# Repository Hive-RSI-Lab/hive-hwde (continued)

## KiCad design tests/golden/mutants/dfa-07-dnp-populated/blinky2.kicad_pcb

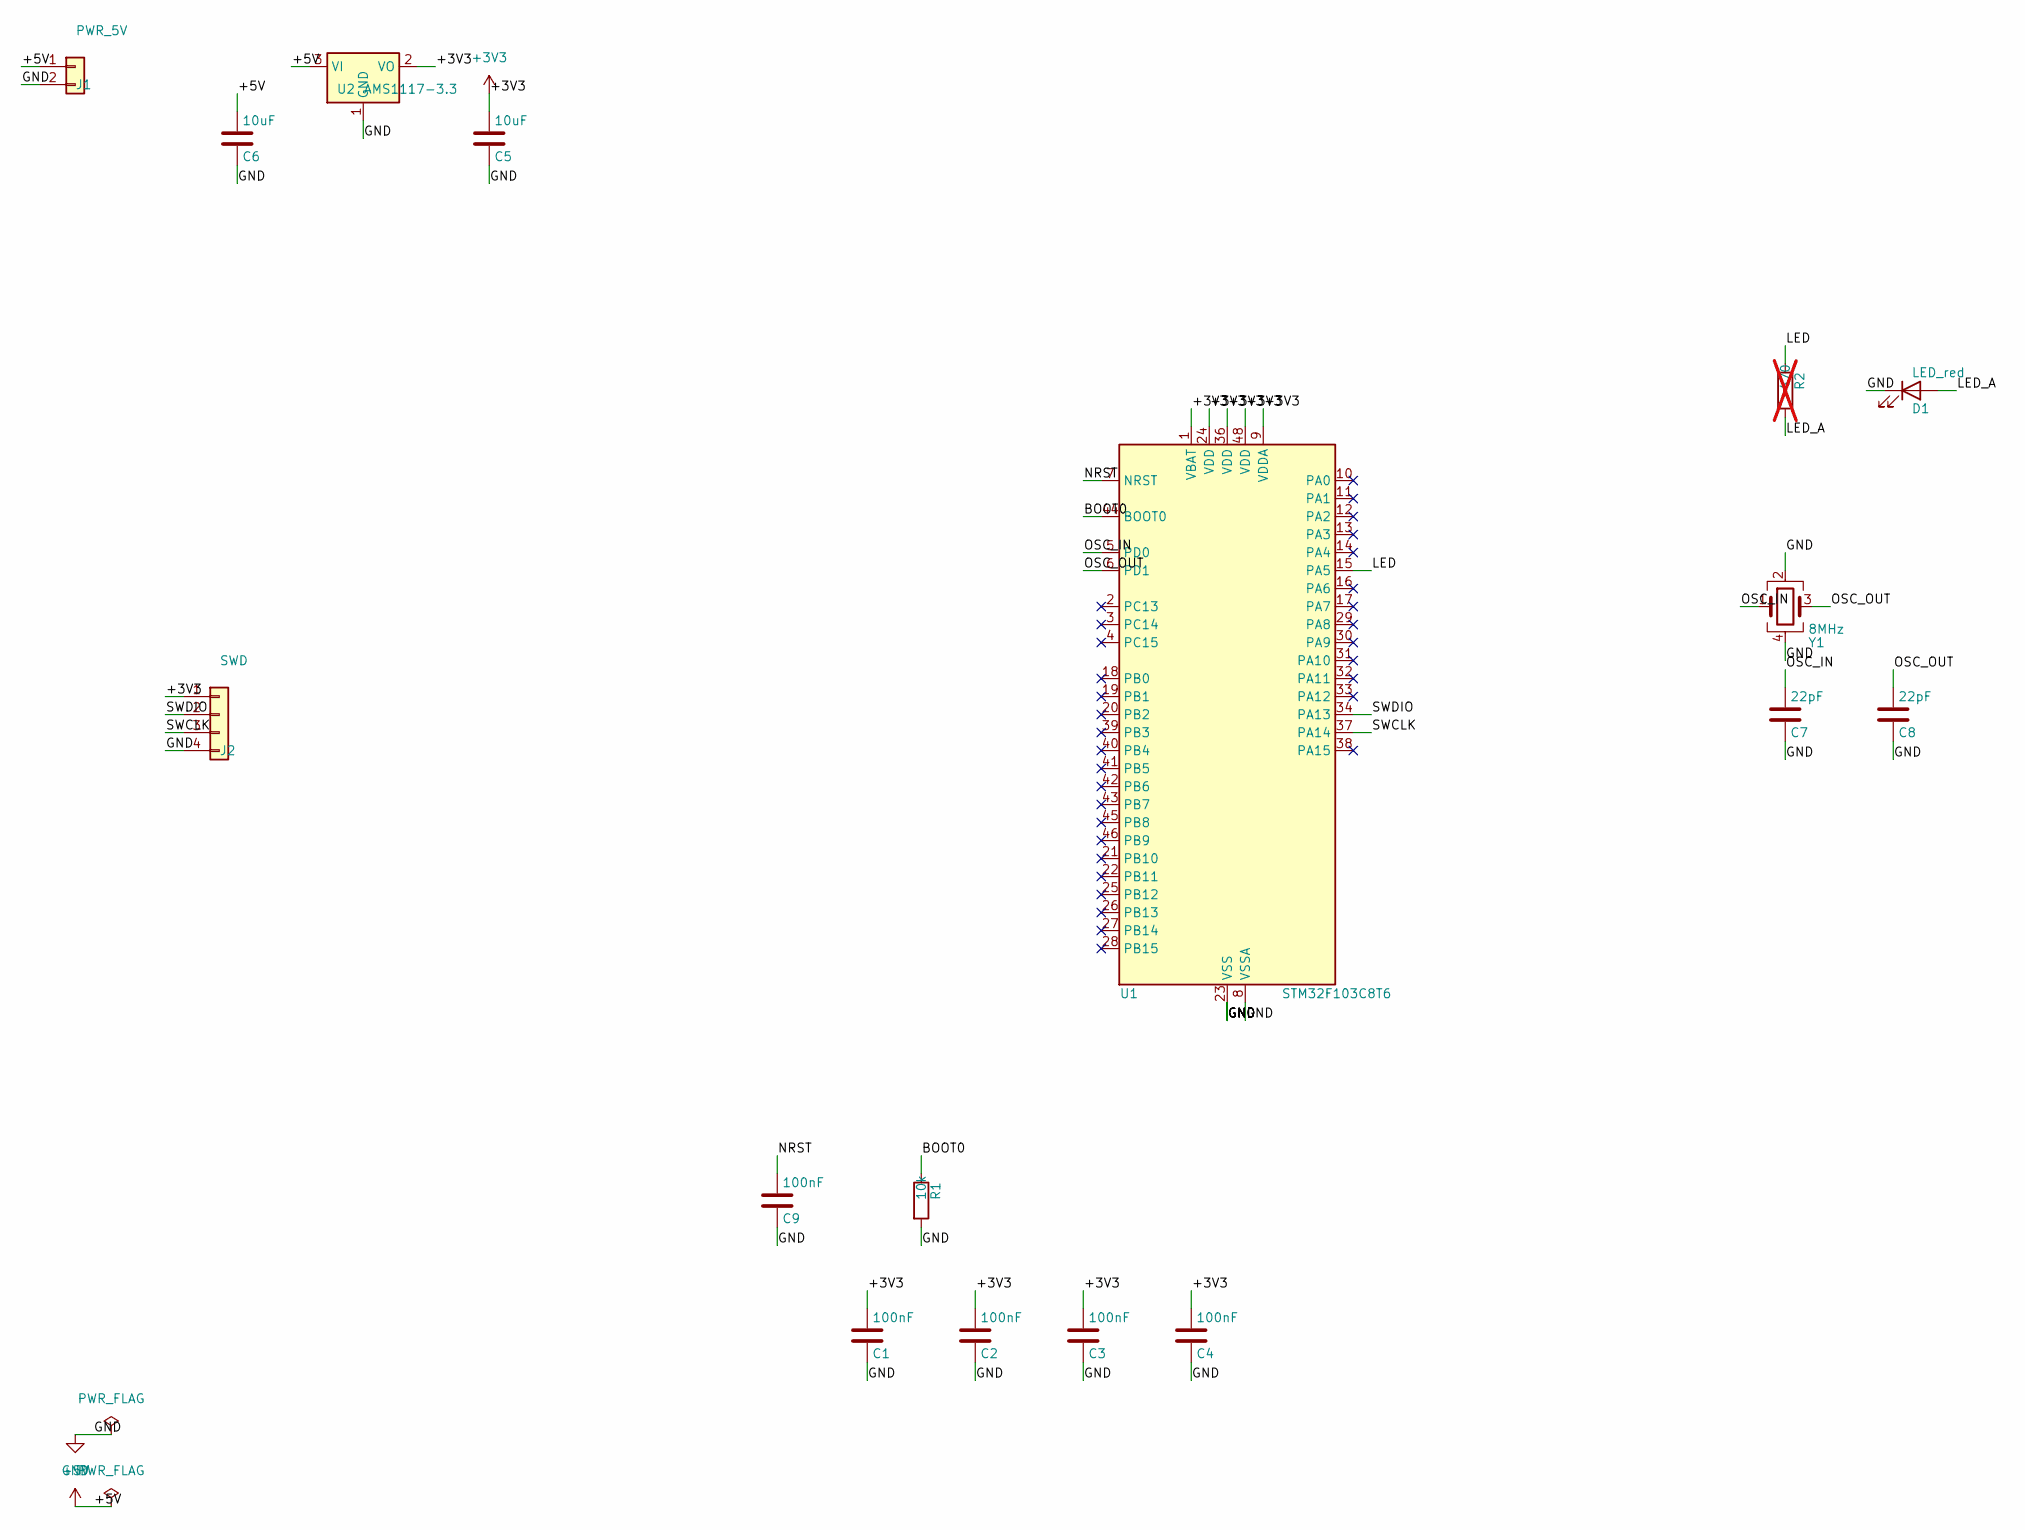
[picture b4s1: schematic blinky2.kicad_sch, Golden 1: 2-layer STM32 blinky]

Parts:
C1, C2, C3, C4, C9: 100nF; C_0603_1608Metric
C5, C6: 10uF; C_0805_2012Metric
C7, C8: 22pF; C_0603_1608Metric
D1: LED_red; LED_0805_2012Metric
J1: PWR_5V; PinHeader_1x02_P2.54mm_Vertical
J2: SWD; PinHeader_1x04_P2.54mm_Vertical
R1: 10k; R_0603_1608Metric
R2: 470; R_0603_1608Metric; not fitted
U1: STM32F103C8T6; LQFP-48_7x7mm_P0.5mm
U2: AMS1117-3.3; SOT-223-3_TabPin2
Y1: 8MHz; Crystal_SMD_3225-4Pin_3.2x2.5mm

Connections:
+3V3: C1.1, C2.1, C3.1, C4.1, C5.1, J2.1, U1.1 (VBAT), U1.9 (VDDA), U1.24 (VDD), U1.36 (VDD), U1.48 (VDD), U2.2 (VO)
+5V: C6.1, J1.1, U2.3 (VI)
/BOOT0: R1.1, U1.44 (BOOT0)
/LED: R2.1, U1.15 (PA5)
/LED_A: D1.2 (A), R2.2
/NRST: C9.1, U1.7 (NRST)
/OSC_IN: C7.1, U1.5 (PD0), Y1.1
/OSC_OUT: C8.1, U1.6 (PD1), Y1.3
/SWCLK: J2.3, U1.37 (PA14)
/SWDIO: J2.2, U1.34 (PA13)
GND: C1.2, C2.2, C3.2, C4.2, C5.2, C6.2, C7.2, C8.2, C9.2, D1.1 (K), J1.2, J2.4, R1.2, U1.8 (VSSA), U1.23 (VSS), U1.35 (VSS), U1.47 (VSS), U2.1 (GND), Y1.2, Y1.4

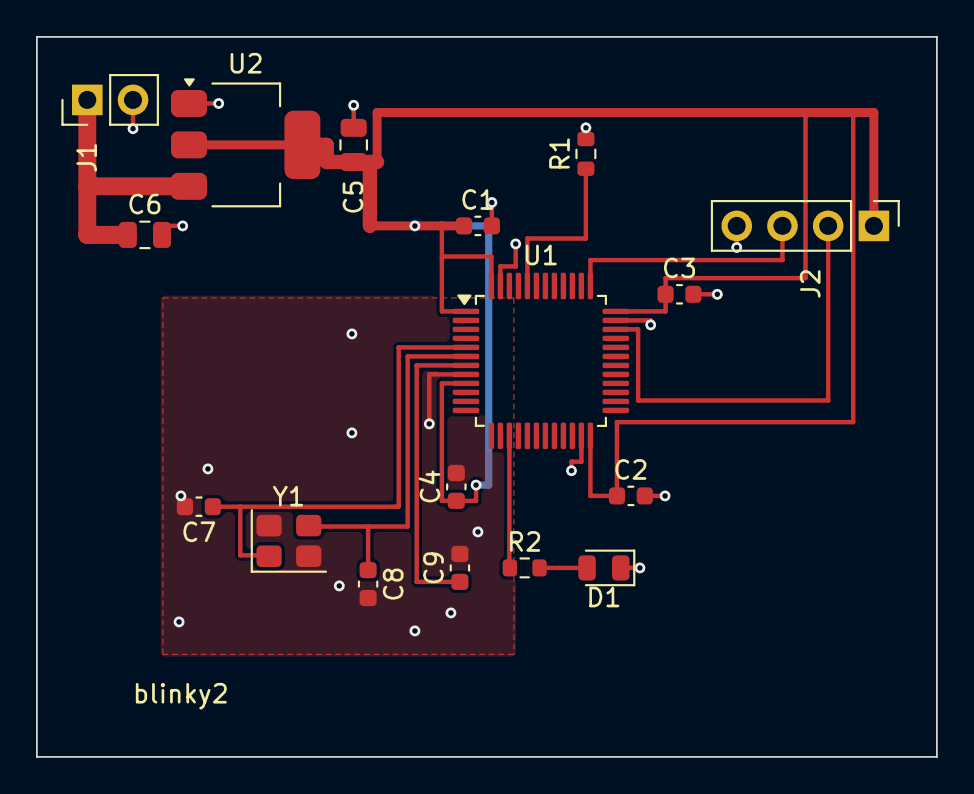
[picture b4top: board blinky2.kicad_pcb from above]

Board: 2 copper layers, 50.0 x 40.0 mm, 17 parts (0 on the bottom side), 11 nets.

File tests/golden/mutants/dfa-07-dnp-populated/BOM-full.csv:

Comment,Designator,Qty Per Board,Footprint,MPN,LCSC,Assembly Class,Instructions
PWR_5V,J1,1,PinHeader_1x02_P2.54mm_Vertical,,,smt_placed,
SWD,J2,1,PinHeader_1x04_P2.54mm_Vertical,,,smt_placed,
22pF,"C8,C7",2,C_0603_1608Metric,,,smt_placed,
10uF,"C5,C6",2,C_0805_2012Metric,,,smt_placed,
8MHz,Y1,1,Crystal_SMD_3225-4Pin_3.2x2.5mm,,,smt_placed,
100nF,"C9,C1,C2,C3,C4",5,C_0603_1608Metric,,,smt_placed,
10k,R1,1,R_0603_1608Metric,,,smt_placed,
STM32F103C8T6,U1,1,LQFP-48_7x7mm_P0.5mm,,,smt_placed,
AMS1117-3.3,U2,1,SOT-223-3_TabPin2,,,smt_placed,
470,R2,1,R_0603_1608Metric,,,smt_placed,
LED_red,D1,1,LED_0805_2012Metric,,,smt_placed,

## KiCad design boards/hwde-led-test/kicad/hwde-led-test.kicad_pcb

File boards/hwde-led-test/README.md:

# hwde-led-test

A tiny test board that lights one green LED from 5 V. It was the first board the Hive designed with the hwde module, on 2026-10-28, to prove the pipeline runs from brief to checked fab files inside the Hive. It hasn't been ordered. Ordering is the person's call.

## What it is

- 2 layers, 1.6 mm FR-4, HASL, 13.4 x 10.5 mm, no mounting holes.
- **J1**: a 2-pin 2.54 mm header. Pin 1 (square, marked +) is +5V and pin 2 (marked −) is GND. Use 4.75–5.25 V from a bench supply or a USB 5 V lead.
- **C1**: 4.7 µF 16 V X5R 0603 across the input, next to J1.
- **R1 + D1**: a 470 Ω resistor feeds a green 0603 LED (KT-0603G). The LED runs at 3.5–4.6 mA over the input range.
- The bottom layer is a GND pour, and all parts are SMD on the top except J1.

| Ref | Part | LCSC | JLC |
|---|---|---|---|
| J1 | PZ254V-11-02P 1x2 header | C492401 | Extended |
| C1 | CL10A475KO8NNNC 4.7 µF 16 V | C19666 | Basic |
| R1 | 0603WAF4700T5E 470 Ω 1 % | C23179 | Basic |
| D1 | KT-0603G green LED | C12624 | Extended |

## Design decisions, and why

- **R1 is 470 Ω, not the 680 Ω the architecture first proposed.** The LED's listed forward voltage is 3.1 V at 5 mA, and at that voltage 680 Ω gives only 2.4–2.8 mA. 470 Ω gives 3.5–4.6 mA. The 3.1 V figure comes from the LCSC listing because the datasheet wouldn't download. If the real forward voltage is as high as 3.4 V, the current at 4.75 V input drops to about 2.8 mA, and the LED is still lit.
- **D1 is a JLC Extended part.** There is no Basic 0603 green LED, and the brief asked for 0603.
- **There is no reverse-polarity protection, as the brief asked.** A swapped lead puts up to 5.25 V reverse across D1. The silk marks + and − at J1 to make that less likely.
- **The size was earned by placement.** After placement the outline was fitted with a 2 mm margin, because at the time `board_edit --outline fit` didn't count reference text and smaller margins clipped it. It was then grown to 10.5 mm tall because the skill's JLC capabilities file gives 10 mm as the assembly minimum. `fit` now counts all silk: at its default 1 mm margin it gives 13.21 x 9.95 mm, which the 10 mm minimum would grow again, so the 13.4 x 10.5 mm outline stays. `board_edit --outline keep --report-only` finds no silk it clips.
- **The 0603 courtyards are the pads plus 0.25 mm.** The EasyEDA footprints came with the body outline (±0.80 x ±0.40 mm) as the courtyard, inside the pads. They were first widened by hand; now `fpfix` rule E rebuilds them, on every `lib_pull` and on the placed copies with `fpfix.py --pcb`: C0603 ±1.35 x ±0.70, LED0603-RD ±1.40 x ±0.65, R0603 ±1.45 x ±0.70 mm. The verify suite's `check_courtyard` fails a board whose courtyards miss their pads.

Every decision is also in `state.json` (`decisions`), stage by stage in `log/P*-digest.md`, and with what it taught in `LEARNINGS.md`.

## The report

[`report/hwde-led-test-report.pdf`](report/hwde-led-test-report.pdf) (source: [`report/hwde-led-test-report.md`](report/hwde-led-test-report.md)) has the whole board in one place: schematic, copper layers, 3D renders, BOM and cost, every gate, the sign-offs and waivers still waiting for the person, and the run's time per stage and snags. `report/build.sh` rebuilds it.

hwde's own design document, [`reports/design_doc/hwde-led-test-design-doc.pdf`](reports/design_doc/hwde-led-test-design-doc.pdf), is the engineering record in the house style: every gate, decision and stage digest. `hwde report_gen --workspace boards/hwde-led-test` rebuilds it.

## The checks it passed

| Gate | Result |
|---|---|
| ERC (`erc`) | 0 errors, 0 warnings |
| Placement (`place`) | pass |
| Routed DRC (`drc_routed`) | 0 errors, 0 warnings, 0 unconnected |
| Verify suite (`verify`, 14 checks) | pass, with 2 warnings: a 0.15 mm jog on /LED_A, and D1 (an LED) with no voltage-rating attribute |
| JLC DFM on the exported Gerbers (`dfm`) | 0 findings |

A fresh-context reviewer read the schematic and the board (`reports/review-schematic.md`, `reports/review-board.md`) and found 0 errors.

## How to rebuild and re-check it

From a checkout of hive-hwde, with the module's `bin/hwde` (see `docs/README.md`):

```sh
cd boards/hwde-led-test
eval "$(../../bin/hwde env)"
PYTHONPATH=$HWDE_SKILL/scripts:$HWDE_SKILL/scripts/lib $HWDE_PY kicad/gen/root.py   # schematic + decoupling.json, rebuilt in place (keeps its UUIDs)
../../bin/hwde lib_pull --parts parts/parts.json --project kicad   # 3D models (not committed); the parts in lib/ stay as they are
for g in erc place drc_routed verify dfm; do f=kicad/hwde-led-test.kicad_pcb; [ $g = erc ] && f=kicad/hwde-led-test.kicad_sch; ../../bin/hwde gate --gate $g $f --workspace .; done
../../bin/hwde fab_export --pcb kicad/hwde-led-test.kicad_pcb --out-dir fab
../../bin/hwde bom_cpl --pcb kicad/hwde-led-test.kicad_pcb --out-dir fab --parts parts/parts.json
```

The fab package is in `fab/`: `hwde-led-test_gerbers.zip`, `BOM.csv`, `CPL.csv` and `prebuy.csv`. Both Extended parts may need to be bought into JLC inventory first.

## How to test a built board

Set a bench supply to 5.0 V with a 50 mA limit and connect it to J1, + to pin 1. The supply should read about 4 mA and the LED should light green. If the LED stays dark at about 0 mA, check the polarity first.

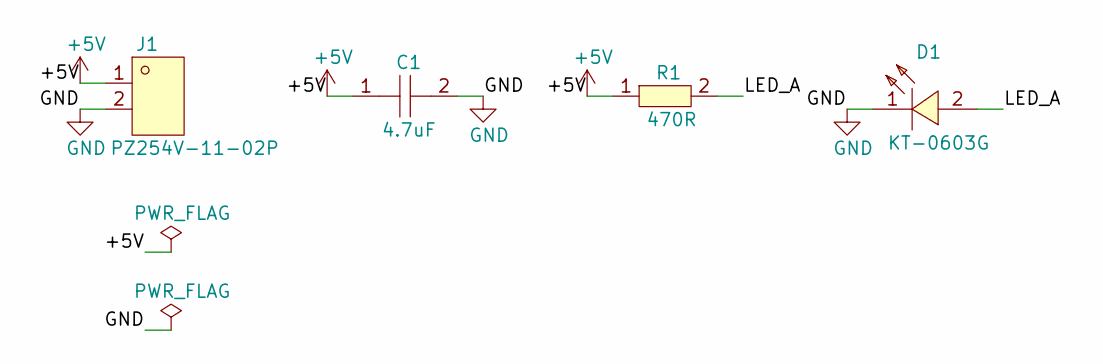
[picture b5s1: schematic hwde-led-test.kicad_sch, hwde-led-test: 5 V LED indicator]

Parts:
C1: 4.7uF; C0603
D1: KT-0603G; LED0603-RD
J1: PZ254V-11-02P; HDR-TH_2P-P2.54-V-M
R1: 470R; R0603

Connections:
+5V: C1.1, J1.1, R1.1
/LED_A: D1.2 (A), R1.2
GND: C1.2, D1.1 (K), J1.2

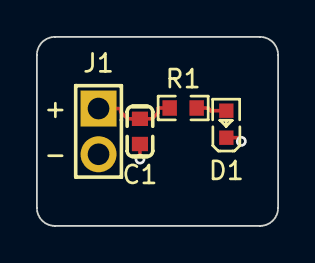
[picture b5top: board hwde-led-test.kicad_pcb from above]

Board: 2 copper layers, 13.4 x 10.5 mm, 4 parts (0 on the bottom side), 3 nets.

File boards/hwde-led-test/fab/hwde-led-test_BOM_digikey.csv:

Digi-Key Part Number,Manufacturer Name,Manufacturer Part Number,Customer Reference,Quantity 1,Notes,Description,LCSC,Stock,Unit Price (USD),Extended Price (USD)
,Samsung Electro-Mechanics,CL10A475KO8NNNC,C1,1,smt_placed,4.7uF,C19666,,,
,Hubei KENTO Elec,KT-0603G,D1,1,smt_placed,KT-0603G,C12624,,,
,UNI-ROYAL,0603WAF4700T5E,R1,1,smt_placed,470R,C23179,,,
,XFCN,PZ254V-11-02P,J1,1,tht,PZ254V-11-02P,C492401,,,

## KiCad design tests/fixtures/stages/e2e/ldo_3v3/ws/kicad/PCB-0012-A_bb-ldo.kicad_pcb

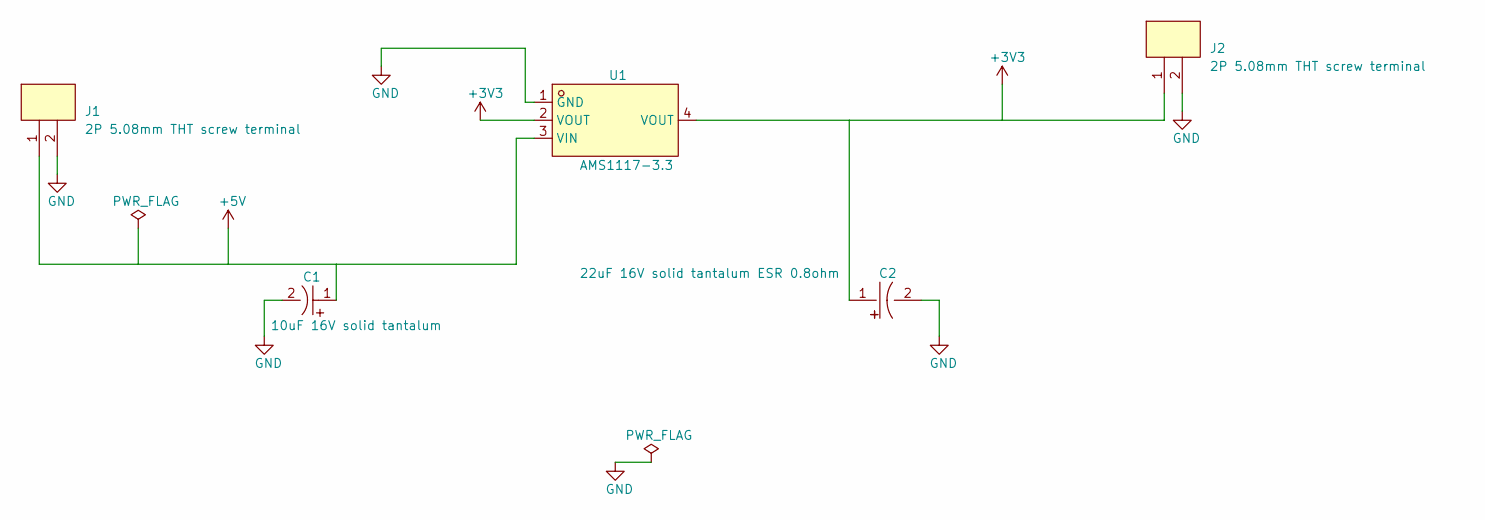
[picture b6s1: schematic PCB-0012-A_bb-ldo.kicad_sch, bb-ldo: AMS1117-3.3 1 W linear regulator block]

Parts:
C1: 10uF 16V solid tantalum; CAP-SMD_L3.2-W1.6-RD-C7171; LCSC C7171
C2: 22uF 16V solid tantalum ESR 0.8ohm; CAP-SMD_L7.3-W4.3; LCSC C215872
J1, J2: 2P 5.08mm THT screw terminal; CONN-TH_2P-P5.00_WJ500V-5.08-2P; LCSC C8465
U1: AMS1117-3.3; SOT-223-3_L6.5-W3.4-P2.30-LS7.0-BR; LCSC C6186

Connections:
+3V3: C2.1, J2.1, U1.2 (VOUT), U1.4 (VOUT)
+5V: C1.1, J1.1, U1.3 (VIN)
GND: C1.2, C2.2, J1.2, J2.2, U1.1 (GND)

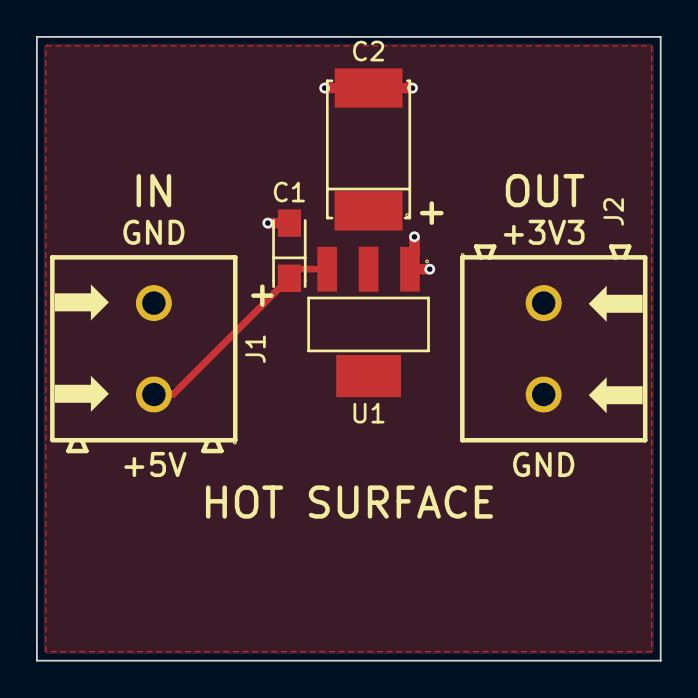
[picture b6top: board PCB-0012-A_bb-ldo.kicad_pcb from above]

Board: 2 copper layers, 34.7 x 34.7 mm, 5 parts (0 on the bottom side), 3 nets.

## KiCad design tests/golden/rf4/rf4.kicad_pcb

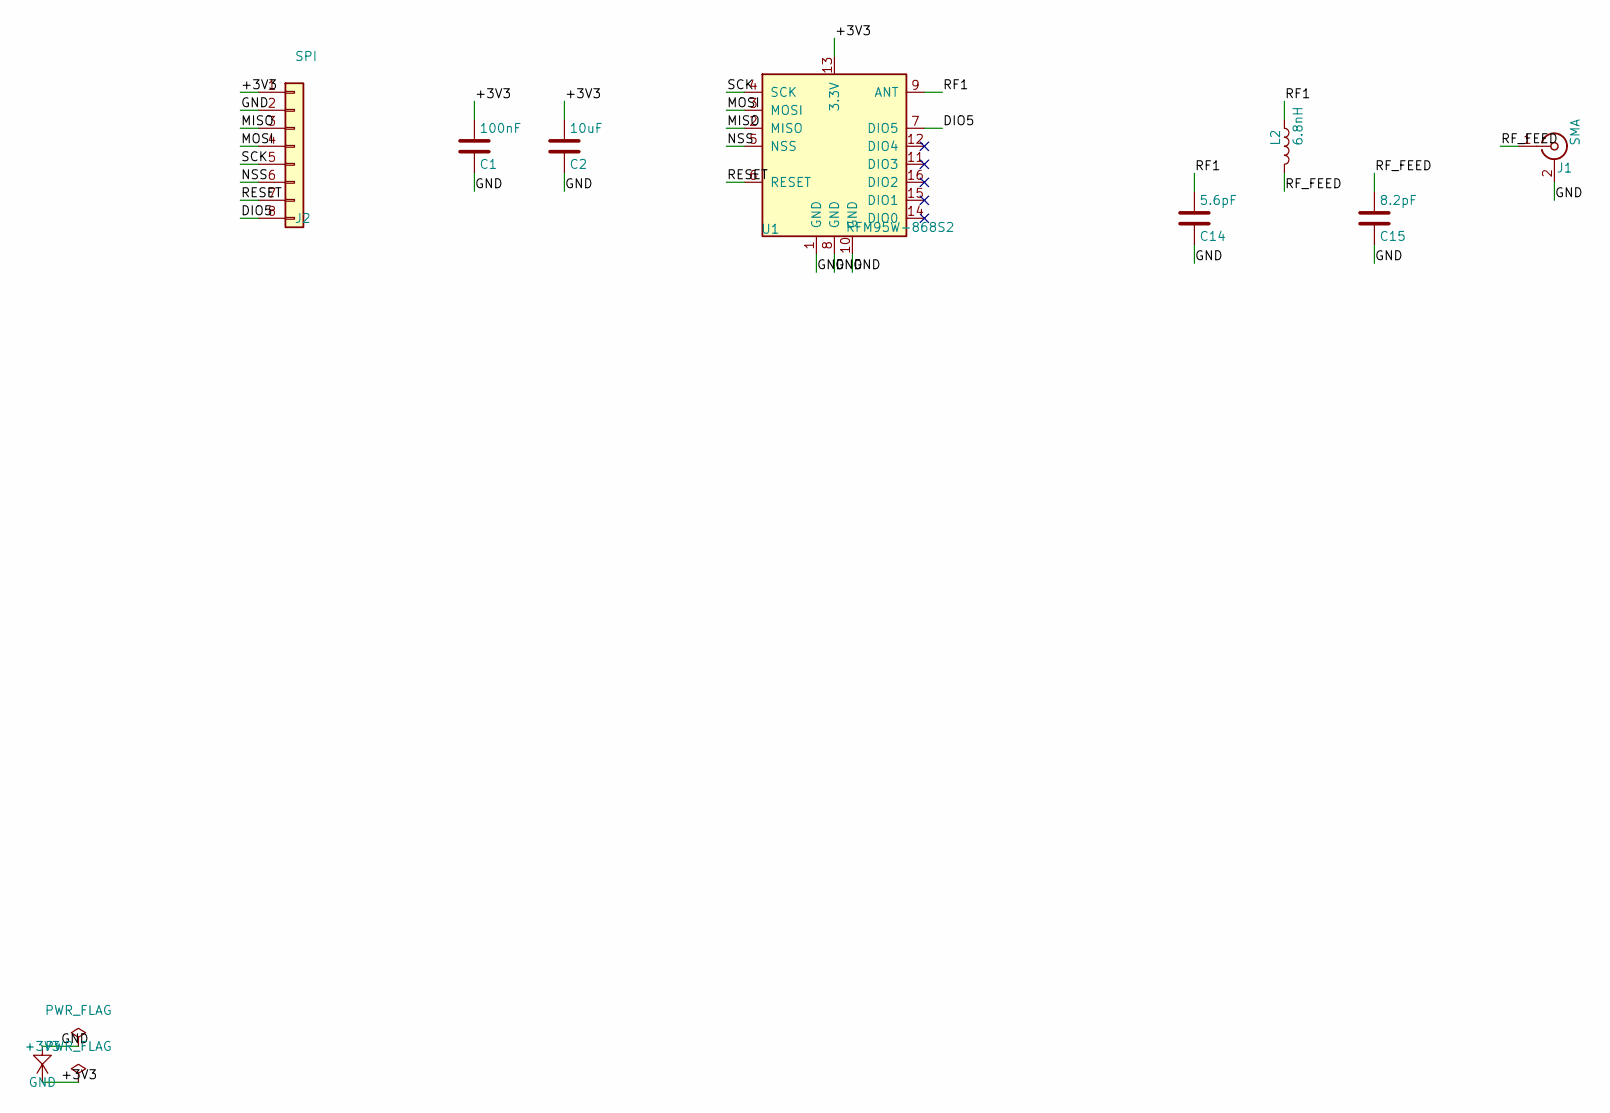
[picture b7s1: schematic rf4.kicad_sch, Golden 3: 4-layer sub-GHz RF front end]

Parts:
C1: 100nF; C_0603_1608Metric
C2: 10uF; C_0805_2012Metric
C14: 5.6pF; C_0603_1608Metric
C15: 8.2pF; C_0603_1608Metric
J1: SMA; SMA_Amphenol_132289_EdgeMount
J2: SPI; PinHeader_1x08_P2.54mm_Vertical
L2: 6.8nH; L_0603_1608Metric
U1: RFM95W-868S2; HOPERF_RFM9XW_SMD

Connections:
+3V3: C1.1, C2.1, J2.1, U1.13 (3.3V)
/DIO5: J2.8, U1.7 (DIO5)
/MISO: J2.3, U1.2 (MISO)
/MOSI: J2.4, U1.3 (MOSI)
/NSS: J2.6, U1.5 (NSS)
/RESET: J2.7, U1.6 (RESET)
/RF1: C14.1, L2.1, U1.9 (ANT)
/RF_FEED: C15.1, J1.1 (In), L2.2
/SCK: J2.5, U1.4 (SCK)
GND: C1.2, C2.2, C14.2, C15.2, J1.2 (Ext), J2.2, U1.1 (GND), U1.8 (GND), U1.10 (GND)

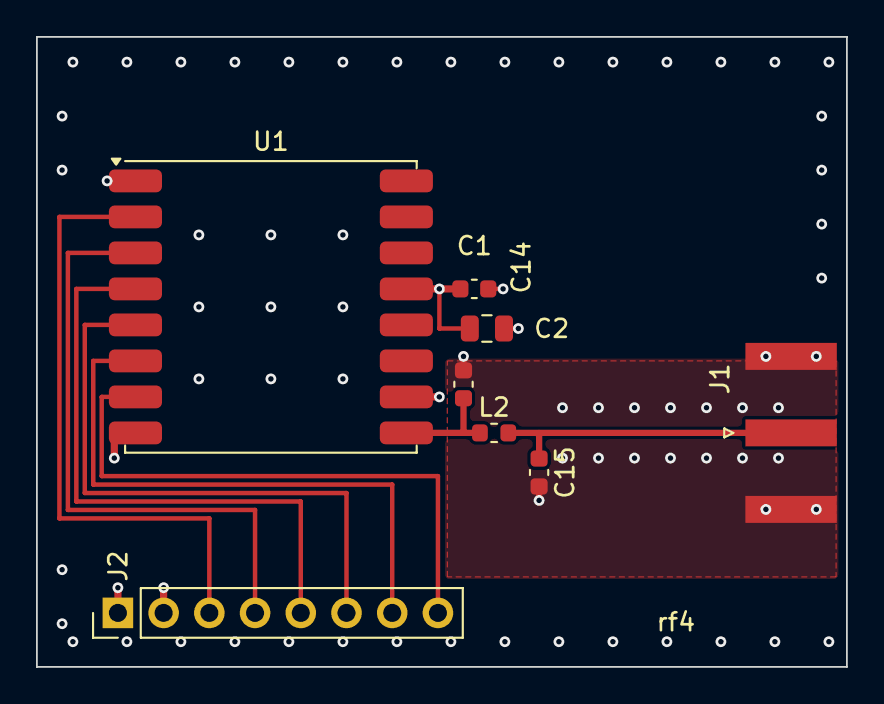
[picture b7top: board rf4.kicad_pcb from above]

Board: 4 copper layers, 45.0 x 35.0 mm, 8 parts (0 on the bottom side), 10 nets.
